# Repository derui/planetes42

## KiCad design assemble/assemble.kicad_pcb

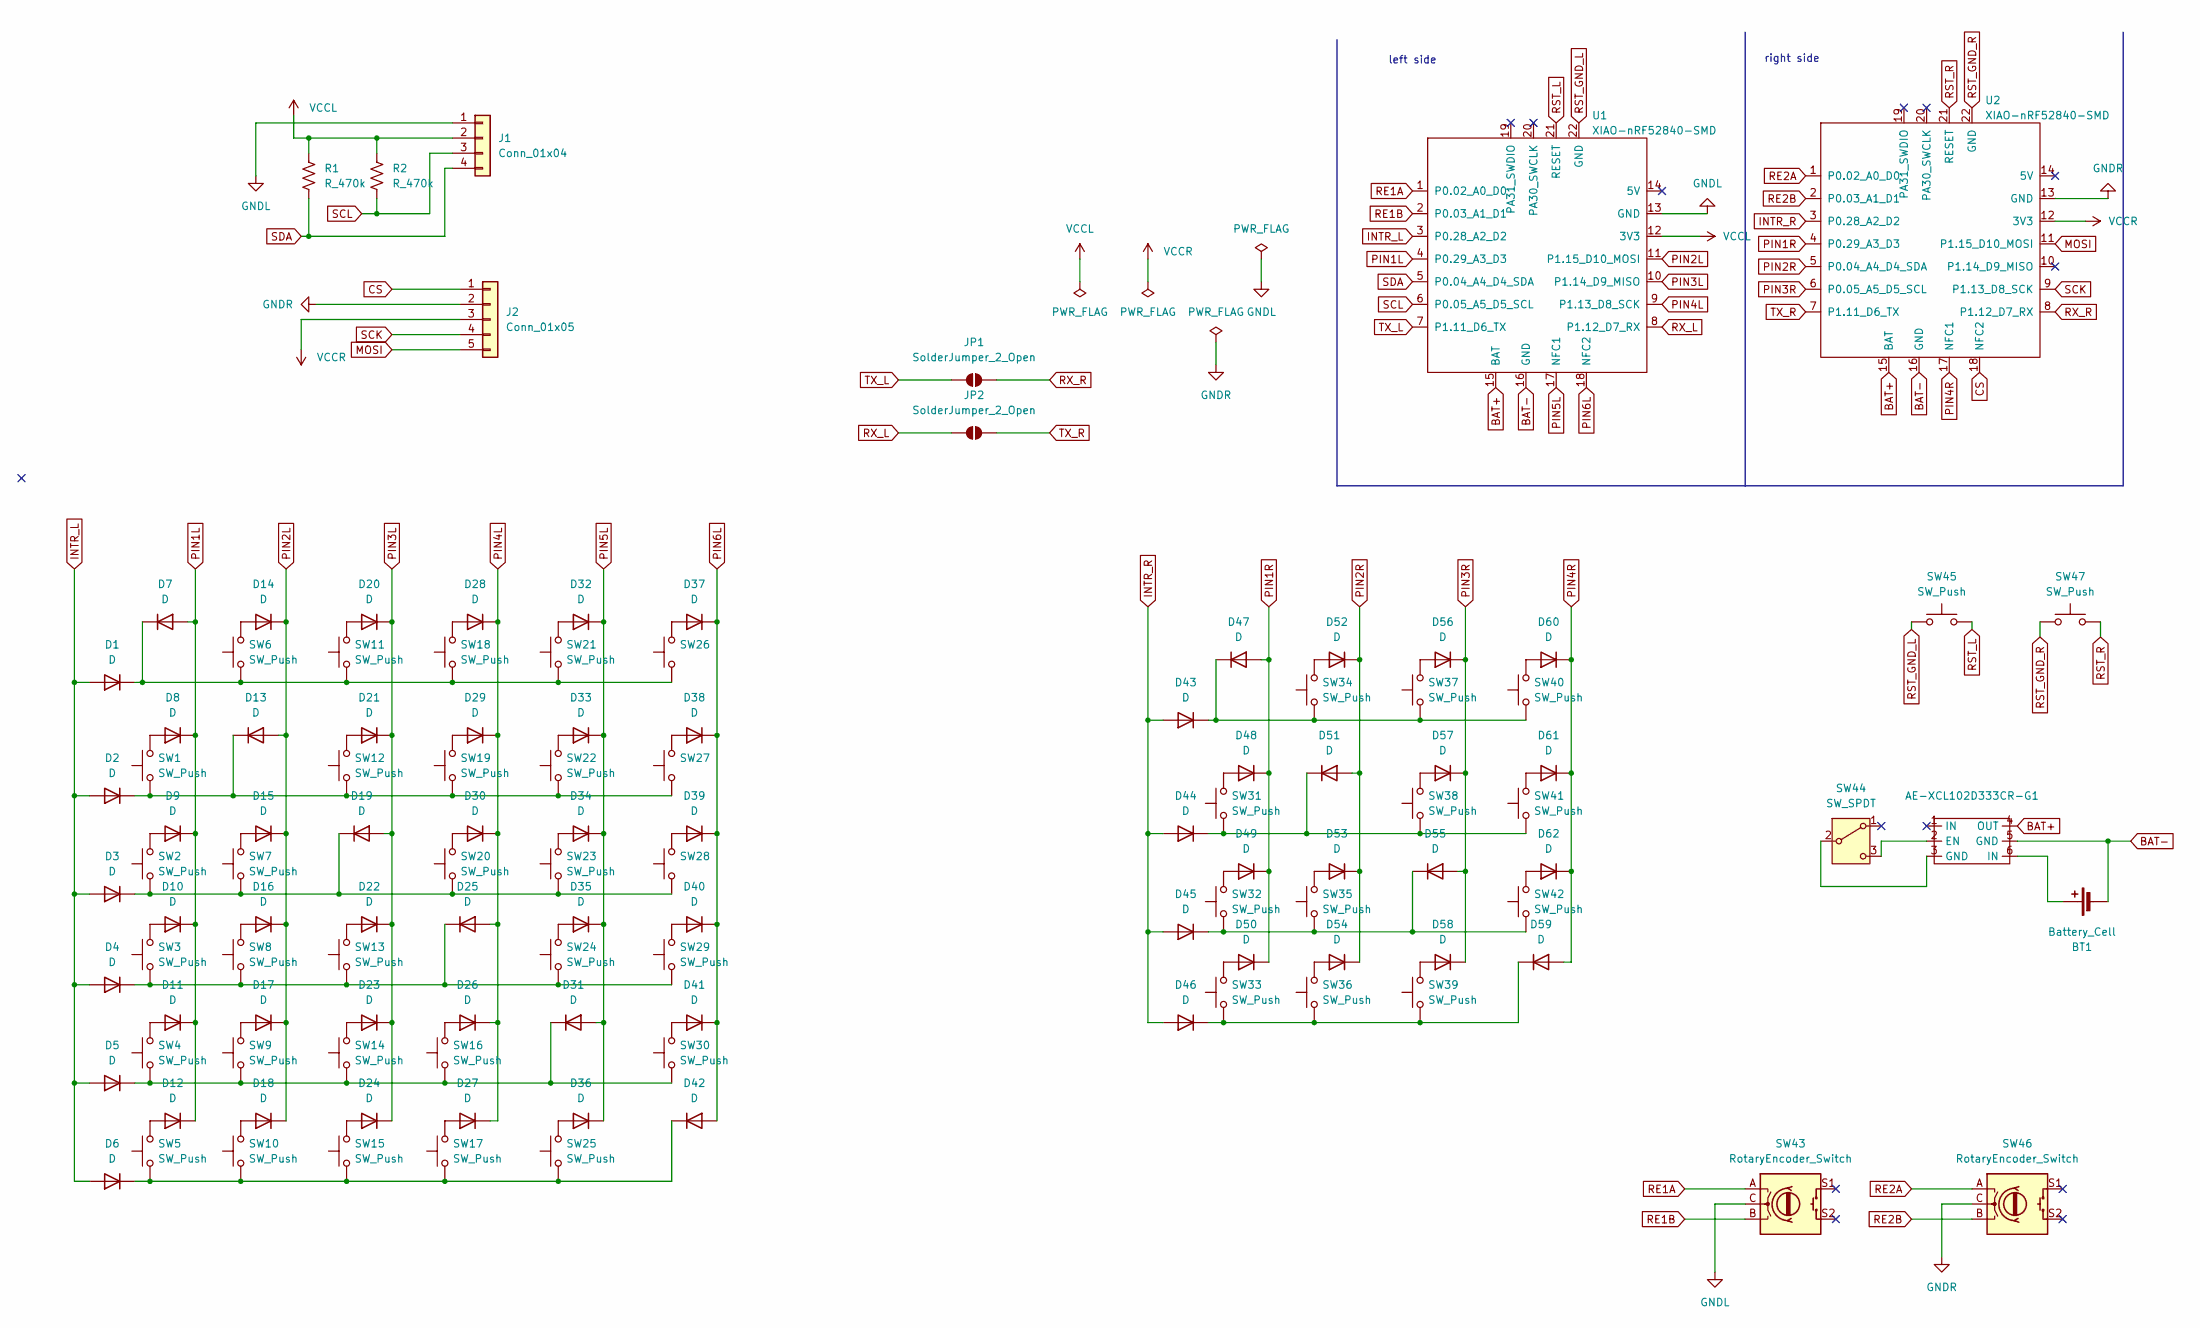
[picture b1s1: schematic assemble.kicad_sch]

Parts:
AE-XCL102D333CR-G1: AE-XCL102D333CR-G
BT1: Battery_Cell; BatteryHolder_Keystone_2460_1xAA
D1, D2, D3, D4, D5, D6, D7, D8, D9, D10, D11, D12, D13, D14, D15, D16, D17, D18, D19, D20, D21, D22, D23, D24, D25, D26, D27, D28, D29, D30, D31, D32, D33, D34, D35, D36, D37, D38, D39, D40, D41, D42, D43, D44, D45, D46, D47, D48, D49, D50, D51, D52, D53, D54, D55, D56, D57, D58, D59, D60, D61, D62: D; Diode_SMD
J1: Conn_01x04; PinSocket_1x04_P2.54mm_Vertical
J2: Conn_01x05; PinHeader_1x05_P2.54mm_Vertical
JP1, JP2: SolderJumper_2_Open; SolderJumper-2_P1.3mm_Open_Pad1.0x1.5mm
R1, R2: R_470k; R_Axial_DIN0204_L3.6mm_D1.6mm_P5.08mm_Horizontal
SW1, SW2, SW3, SW4, SW5, SW6, SW7, SW8, SW9, SW10, SW11, SW12, SW13, SW14, SW15, SW16, SW17, SW18, SW19, SW20, SW21, SW22, SW23, SW24, SW25, SW26, SW27, SW28, SW29, SW30, SW31, SW32, SW33, SW34, SW35, SW36, SW37, SW38, SW39, SW40, SW41, SW42: SW_Push; Choc_v2_Hotswap_1u_16.6
SW43, SW46: RotaryEncoder_Switch; RotaryEncoder_EC12E
SW44: SW_SPDT; TGSW_MSK-12D19
SW45, SW47: SW_Push; ResetSW
U1, U2: XIAO-nRF52840-SMD

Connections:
BAT+: AE-XCL102D333CR-G1.4 (OUT), U1.15 (BAT), U2.15 (BAT)
BAT-: AE-XCL102D333CR-G1.5 (GND), BT1.2 (-), U1.16 (GND), U2.16 (GND)
CS: J2.1, U2.18 (NFC2)
GNDL: J1.1, SW43.C, U1.13 (GND)
GNDR: J2.2, SW46.C, U2.13 (GND)
INTR_L: D1.2 (A), D2.2 (A), D3.2 (A), D4.2 (A), D5.2 (A), D6.2 (A), U1.3 (P0.28_A2_D2)
INTR_R: D43.2 (A), D44.2 (A), D45.2 (A), D46.2 (A), U2.3 (P0.28_A2_D2)
MOSI: J2.5, U2.11 (P1.15_D10_MOSI)
unnamed: AE-XCL102D333CR-G1.2 (EN), SW44.3 (C)
unnamed: AE-XCL102D333CR-G1.6 (IN), BT1.1 (+)
unnamed: D1.1 (K), D7.1 (K), SW6.1, SW11.1, SW18.1, SW21.1, SW26.1
unnamed: D8.2 (A), SW1.2
unnamed: D9.2 (A), SW2.2
unnamed: D10.2 (A), SW3.2
unnamed: D11.2 (A), SW4.2
unnamed: D12.2 (A), SW5.2
unnamed: D2.1 (K), D13.1 (K), SW1.1, SW12.1, SW19.1, SW22.1, SW27.1
unnamed: D14.2 (A), SW6.2
unnamed: D15.2 (A), SW7.2
unnamed: D16.2 (A), SW8.2
unnamed: D17.2 (A), SW9.2
unnamed: D18.2 (A), SW10.2
unnamed: D3.1 (K), D19.1 (K), SW2.1, SW7.1, SW20.1, SW23.1, SW28.1
unnamed: D20.2 (A), SW11.2
unnamed: D21.2 (A), SW12.2
unnamed: D22.2 (A), SW13.2
unnamed: D23.2 (A), SW14.2
unnamed: D24.2 (A), SW15.2
unnamed: D4.1 (K), D25.1 (K), SW3.1, SW8.1, SW13.1, SW24.1, SW29.1
unnamed: D26.2 (A), SW16.2
unnamed: D27.2 (A), SW17.2
unnamed: D28.2 (A), SW18.2
unnamed: D29.2 (A), SW19.2
unnamed: D30.2 (A), SW20.2
unnamed: D5.1 (K), D31.1 (K), SW4.1, SW9.1, SW14.1, SW16.1, SW30.1
unnamed: D32.2 (A), SW21.2
unnamed: D33.2 (A), SW22.2
unnamed: D34.2 (A), SW23.2
unnamed: D35.2 (A), SW24.2
unnamed: D36.2 (A), SW25.2
unnamed: D37.2 (A), SW26.2
unnamed: D38.2 (A), SW27.2
unnamed: D39.2 (A), SW28.2
unnamed: D40.2 (A), SW29.2
unnamed: D41.2 (A), SW30.2
unnamed: D6.1 (K), D42.1 (K), SW5.1, SW10.1, SW15.1, SW17.1, SW25.1
unnamed: D43.1 (K), D47.1 (K), SW34.1, SW37.1, SW40.1
unnamed: D44.1 (K), D51.1 (K), SW31.1, SW38.1, SW41.1
unnamed: D45.1 (K), D55.1 (K), SW32.1, SW35.1, SW42.1
unnamed: D46.1 (K), D59.1 (K), SW33.1, SW36.1, SW39.1
unnamed: D48.2 (A), SW31.2
unnamed: D49.2 (A), SW32.2
unnamed: D50.2 (A), SW33.2
unnamed: D52.2 (A), SW34.2
unnamed: D53.2 (A), SW35.2
unnamed: D54.2 (A), SW36.2
unnamed: D56.2 (A), SW37.2
unnamed: D57.2 (A), SW38.2
unnamed: D58.2 (A), SW39.2
unnamed: D60.2 (A), SW40.2
unnamed: D61.2 (A), SW41.2
unnamed: D62.2 (A), SW42.2
unnamed: AE-XCL102D333CR-G1.3 (GND), SW44.2 (B)
PIN1L: D7.2 (A), D8.1 (K), D9.1 (K), D10.1 (K), D11.1 (K), D12.1 (K), U1.4 (P0.29_A3_D3)
PIN1R: D47.2 (A), D48.1 (K), D49.1 (K), D50.1 (K), U2.4 (P0.29_A3_D3)
PIN2L: D13.2 (A), D14.1 (K), D15.1 (K), D16.1 (K), D17.1 (K), D18.1 (K), U1.11 (P1.15_D10_MOSI)
PIN2R: D51.2 (A), D52.1 (K), D53.1 (K), D54.1 (K), U2.5 (P0.04_A4_D4_SDA)
PIN3L: D19.2 (A), D20.1 (K), D21.1 (K), D22.1 (K), D23.1 (K), D24.1 (K), U1.10 (P1.14_D9_MISO)
PIN3R: D55.2 (A), D56.1 (K), D57.1 (K), D58.1 (K), U2.6 (P0.05_A5_D5_SCL)
PIN4L: D25.2 (A), D26.1 (K), D27.1 (K), D28.1 (K), D29.1 (K), D30.1 (K), U1.9 (P1.13_D8_SCK)
PIN4R: D59.2 (A), D60.1 (K), D61.1 (K), D62.1 (K), U2.17 (NFC1)
PIN5L: D31.2 (A), D32.1 (K), D33.1 (K), D34.1 (K), D35.1 (K), D36.1 (K), U1.17 (NFC1)
PIN6L: D37.1 (K), D38.1 (K), D39.1 (K), D40.1 (K), D41.1 (K), D42.2 (A), U1.18 (NFC2)
RE1A: SW43.A, U1.1 (P0.02_A0_D0)
RE1B: SW43.B, U1.2 (P0.03_A1_D1)
RE2A: SW46.A, U2.1 (P0.02_A0_D0)
RE2B: SW46.B, U2.2 (P0.03_A1_D1)
RST_GND_L: SW45.1, U1.22 (GND)
RST_GND_R: SW47.1, U2.22 (GND)
RST_L: SW45.2, U1.21 (RESET)
RST_R: SW47.2, U2.21 (RESET)
RX_L: JP2.1 (A), U1.8 (P1.12_D7_RX)
RX_R: JP1.2 (B), U2.8 (P1.12_D7_RX)
SCK: J2.4, U2.9 (P1.13_D8_SCK)
SCL: J1.3, R2.2, U1.6 (P0.05_A5_D5_SCL)
SDA: J1.4, R1.2, U1.5 (P0.04_A4_D4_SDA)
TX_L: JP1.1 (A), U1.7 (P1.11_D6_TX)
TX_R: JP2.2 (B), U2.7 (P1.11_D6_TX)
VCCL: J1.2, R1.1, R2.1, U1.12 (3V3)
VCCR: J2.3, U2.12 (3V3)

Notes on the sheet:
left side
right side

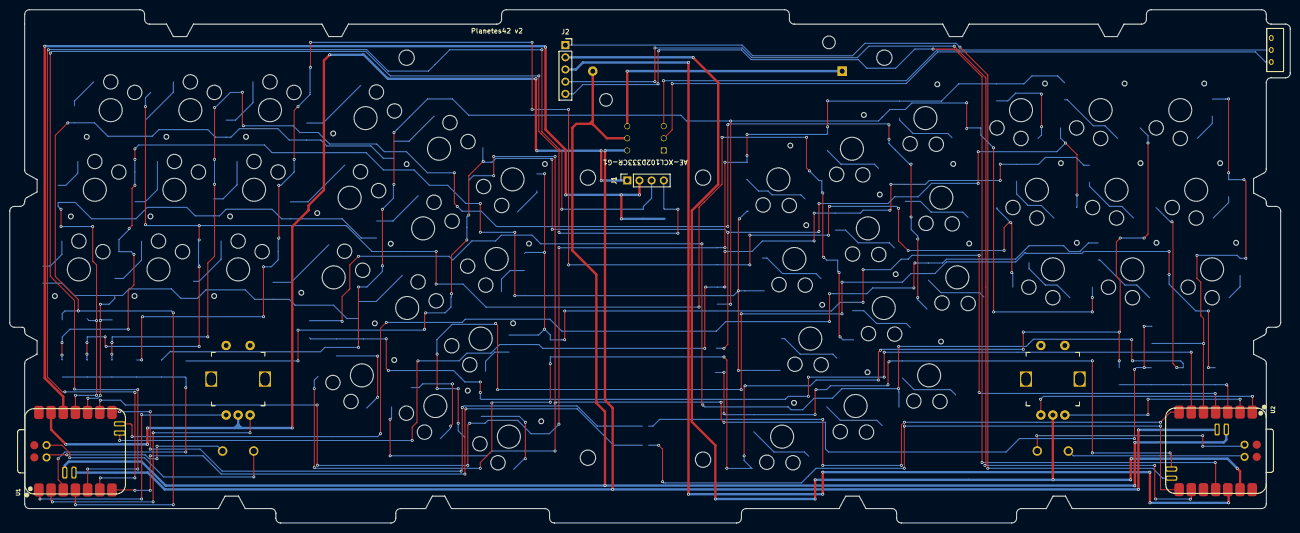
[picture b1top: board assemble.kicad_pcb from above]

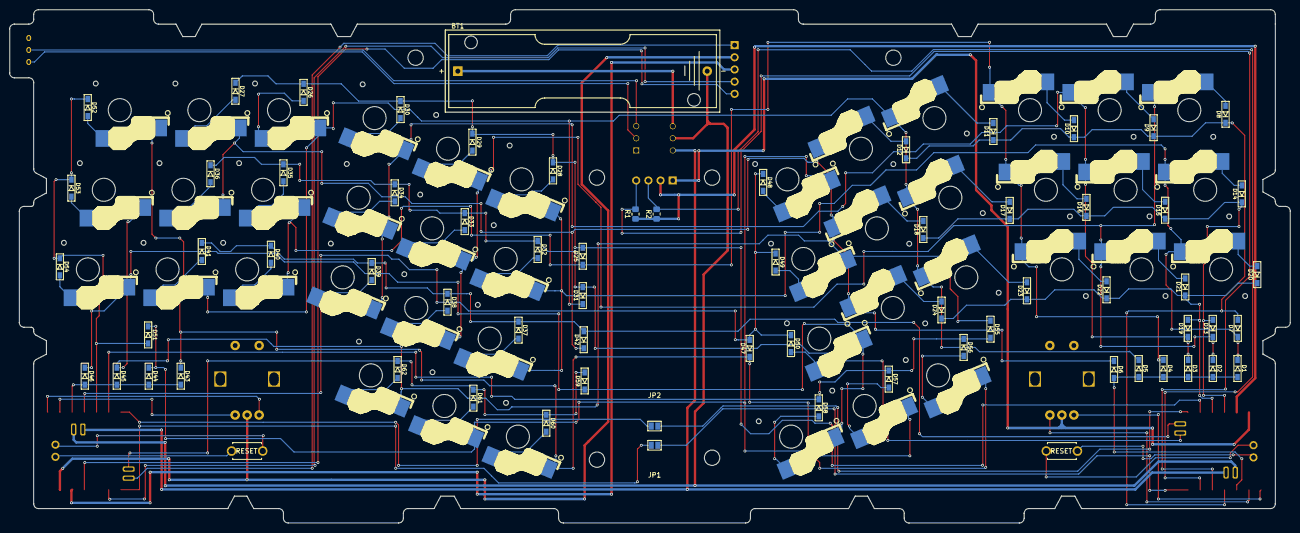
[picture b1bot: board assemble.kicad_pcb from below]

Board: 2 copper layers, 267.0 x 107.0 mm, 125 parts (5 on the bottom side), 90 nets.

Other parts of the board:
Ref**: Val**; m3_Screw_Hole_EdgeCuts
Ref**#2, Ref**#3, Ref**#4, Ref**#5, Ref**#6: Val**; m3_Screw_Hole_EdgeCuts

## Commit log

2025-07-12 feat: add flake.nix
2025-07-19 feat: add base assemble and bottom case data
2025-07-19 feat: implement schematic and PCB partially
2025-07-20 feat: implement some features
2025-07-20 feat: implement PCB
2025-07-24 fix: update screw in PCB
2025-07-24 chore: update flake
2025-07-27 feat: add switch plate
2025-07-28 refactor: start re-wiring
2025-07-28 refactor: finish re-wiring
2025-07-30 fix: update switch plate
2025-08-02 feat: add cases
2025-08-02 feat: add openscad
2025-08-02 feat: add keycap
2025-08-02 fix: width for render
2025-08-09 feat: add some freecad files
2025-08-09 feat: PCB renewal
2025-08-10 feat: implement version 2
2025-08-10 feat: fix convex cap
2025-08-11 fix: change outline
2025-08-11 chore: update nix
2025-08-18 feat: update switch plate
2025-08-18 fix: implement case
2025-08-24 feat: case restructured
2025-08-24 feat: add v3 assemble
2025-08-24 feat: implement v3
2025-08-31 feat: update assemble
2025-09-03 feat: add type bar and delete merged binary
